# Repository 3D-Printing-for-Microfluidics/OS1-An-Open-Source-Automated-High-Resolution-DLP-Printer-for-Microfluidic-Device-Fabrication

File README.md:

# **OS1:** An Open-Source, Automated, High-Resolution DLP Printer for Microfluidic Device Fabrication

Open Source 1 (OS1), an open-source, high-resolution, DLP-based vat photopolymerization platform for fabricating microfluidic devices. Microfluidic function is defined by interconnected negative features, i.e., void regions that form channels, chambers, valves, and other fluidic elements within the printed structure. Accurately producing these features requires high optical resolution, uniform exposure, precise build-surface alignment, and reliable focus control. OS1 addresses these requirements in an automated platform derived from more than 10 years of custom DLP printer development for microfluidics. The printer enables rapid fabrication of microfluidic devices with complex three-dimensional negative-feature geometries that are difficult to achieve using traditional cleanroom-based methods. To reduce dependence on specialized hardware expertise and custom calibration tools, OS1 includes automatic build-surface planarization, automated focus calibration, active focus correction across the build area using a confocal displacement sensor, light-engine power correction using a fiber-optic photodiode sensor, and grayscale image correction for improved irradiance uniformity. These capabilities support repeatable, high-quality fabrication while making advanced microfluidic 3D printing more accessible to other research groups.

This repository is the home to the digital design files for the OS1's hardware, the standalone instruction manual, and the bill of materials.

## CAD

In the CAD folder, step files for the entire printer assmebly and each custom component are included. For parts that are FDM printed, a .3mf file is included. For aluminum parts and polycarbonate parts that are to be cut on a CNC waterjet, a .dxf "Tetris" layout file is included. There are also folders containing the design and manufacturing files for 2 custom printed circuit boards.

## Bill of Materials

The Bill of Materials is contained in a Microsoft Excel spreadsheet (.xlsx). It is oraganized into subassembly groups to match the instruction manual.

## Supplemental

The Visitech LRS WQ light engine utilized in this platform has been discontinued and replaced with an LRS WQ Plus light engine. This new version is not compatible with the current OS1 software and has not been validated with our platform; however, the full STEP assembly for the updated version and an alternate instruction manual are available in the supplemental information. Note on printer software: the LRS WQ Plus is a major revision of the LRS platform and uses a new communication protocol from the previous version. To implement the new LRS WQ Plus, a new hardware driver will need to be written which does not rely on HDMI data transfer from the Raspberry Pi.

Included in the supplemental materials is also a set of videos detailing specific parts of printer construction, operation, and maintenance.

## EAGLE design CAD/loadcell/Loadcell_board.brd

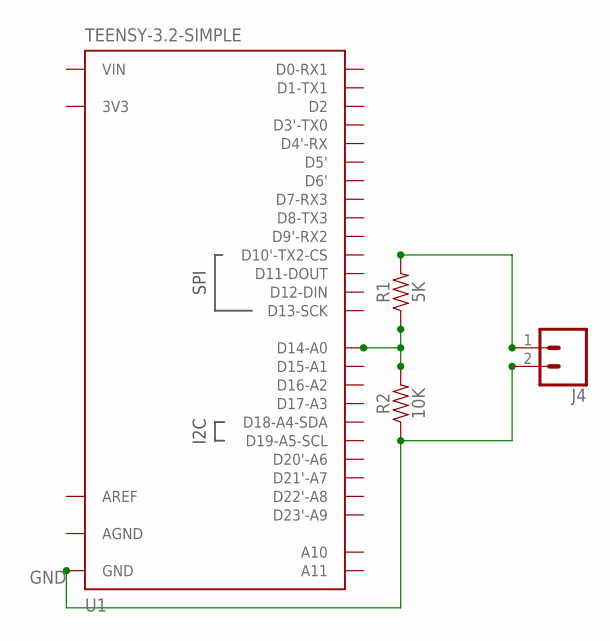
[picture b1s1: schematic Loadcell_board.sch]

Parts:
J4: CONN_02; 1X02
R1: 5K; AXIAL-0.3
R2: 10K; AXIAL-0.3
U1: TEENSY-3.2-SIMPLE

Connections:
3V3: U1.3.3V (3V3)
AGND: U1.AGND
AREF: U1.AREF
GND: J4.2, R2.P$1 (1), U1.GND
unnamed: R1.P$1 (1), R2.P$2 (2), U1.14 (D14-A0)
unnamed: J4.1, R1.P$2 (2)
VIN: U1.VIN

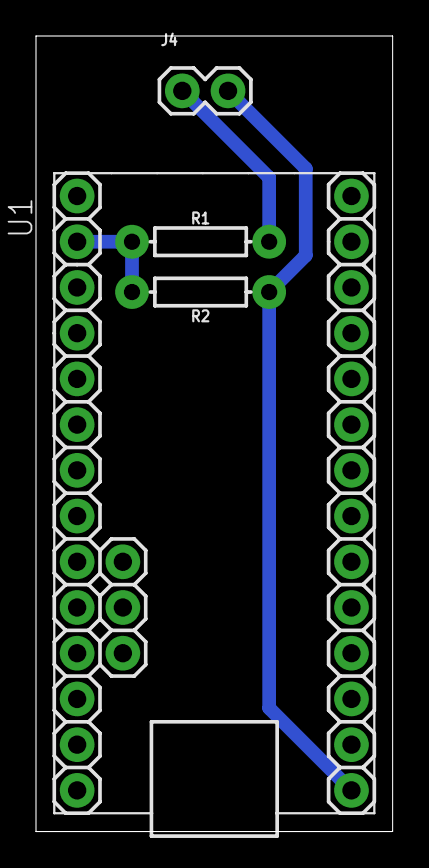
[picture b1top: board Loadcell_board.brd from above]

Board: 2 copper layers, 19.8 x 44.2 mm, 4 parts (0 on the bottom side), 3 nets.

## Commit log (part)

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2026-05-05 Added CAD
2026-05-05 Instruction PDFs added
2026-05-13 added BOM
2026-06-05 License added
2026-06-05 moved
2026-06-08 updated 6/8/26

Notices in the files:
parts and their libraries:
SparkFun-Connectors: Licensing: Creative Commons ShareAlike 4.0 International - https://creativecommons.org/licenses/by-sa/4.0
